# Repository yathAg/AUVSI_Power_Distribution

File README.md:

# AUVSI_Power_Distribution

This project includes the PCBS designed for the Seraphim , the Hex-rotor by PROJECT MANAS that participated in AUVSI SUAS 2022

The unavailibility of cheap and reliable power distribution systems called for designing a fully custom solution that powers the following :-
- Six T-Motor P60 170 Kv motors
- PixHawk Cube Orange
- RFD900X Telemetry Radio
- UGV Winch mechanism

The onboard electronic components are powered by
- Two 6S 32000 mAh LiPO Batteries for the Motors
- One 3S 4200 mAh LiPO Battery for control electronics

**The project includes three pcbs:**

## Power distribution pcb

A simple distributor pcb which can have upto 12 motors:
2 Oz thickness for more current
Exposed copper for heat sink
Voltage sense capability using the voltage from balance connector
Mosfets to shut down current flow when required

## Current sensing pcb  
This pcb is based on the allegro asc772 current sensor
The 400 amp variant was avoided due to unavailability
The 200 amp variant was chosen
2 boards will be used in order to measure separate packs in parallel
Output is a analog value of 5v
The board can also measure voltage levels

## Power HUB

This pcb incorporates the buck and boost modules
1x5v buck ( df13)
2x 5v buck ( ph)
1x 7.4v buck
Current sense mixer

The lmr33640 ic was chosen due to wide input range and 4 amp current output
All bucks were separated
Low space design
Can mix to current sensor values using opamp circuit
Reverse polarity protection

## Pcb design learnings from the project
- No thermals in high current pads
- Avoid choke points ( traces that make current flow path longer)
- Switching loops of power converters have to be as small as possible
- output trace thickness
- Placement of decoupling caps
- Using keepots to avoid traces being to close
- Appropriate pad sizes with vias for current conduction

All schematics , pcb images, and gerber files have been added
The gerbers were formatted for panelization

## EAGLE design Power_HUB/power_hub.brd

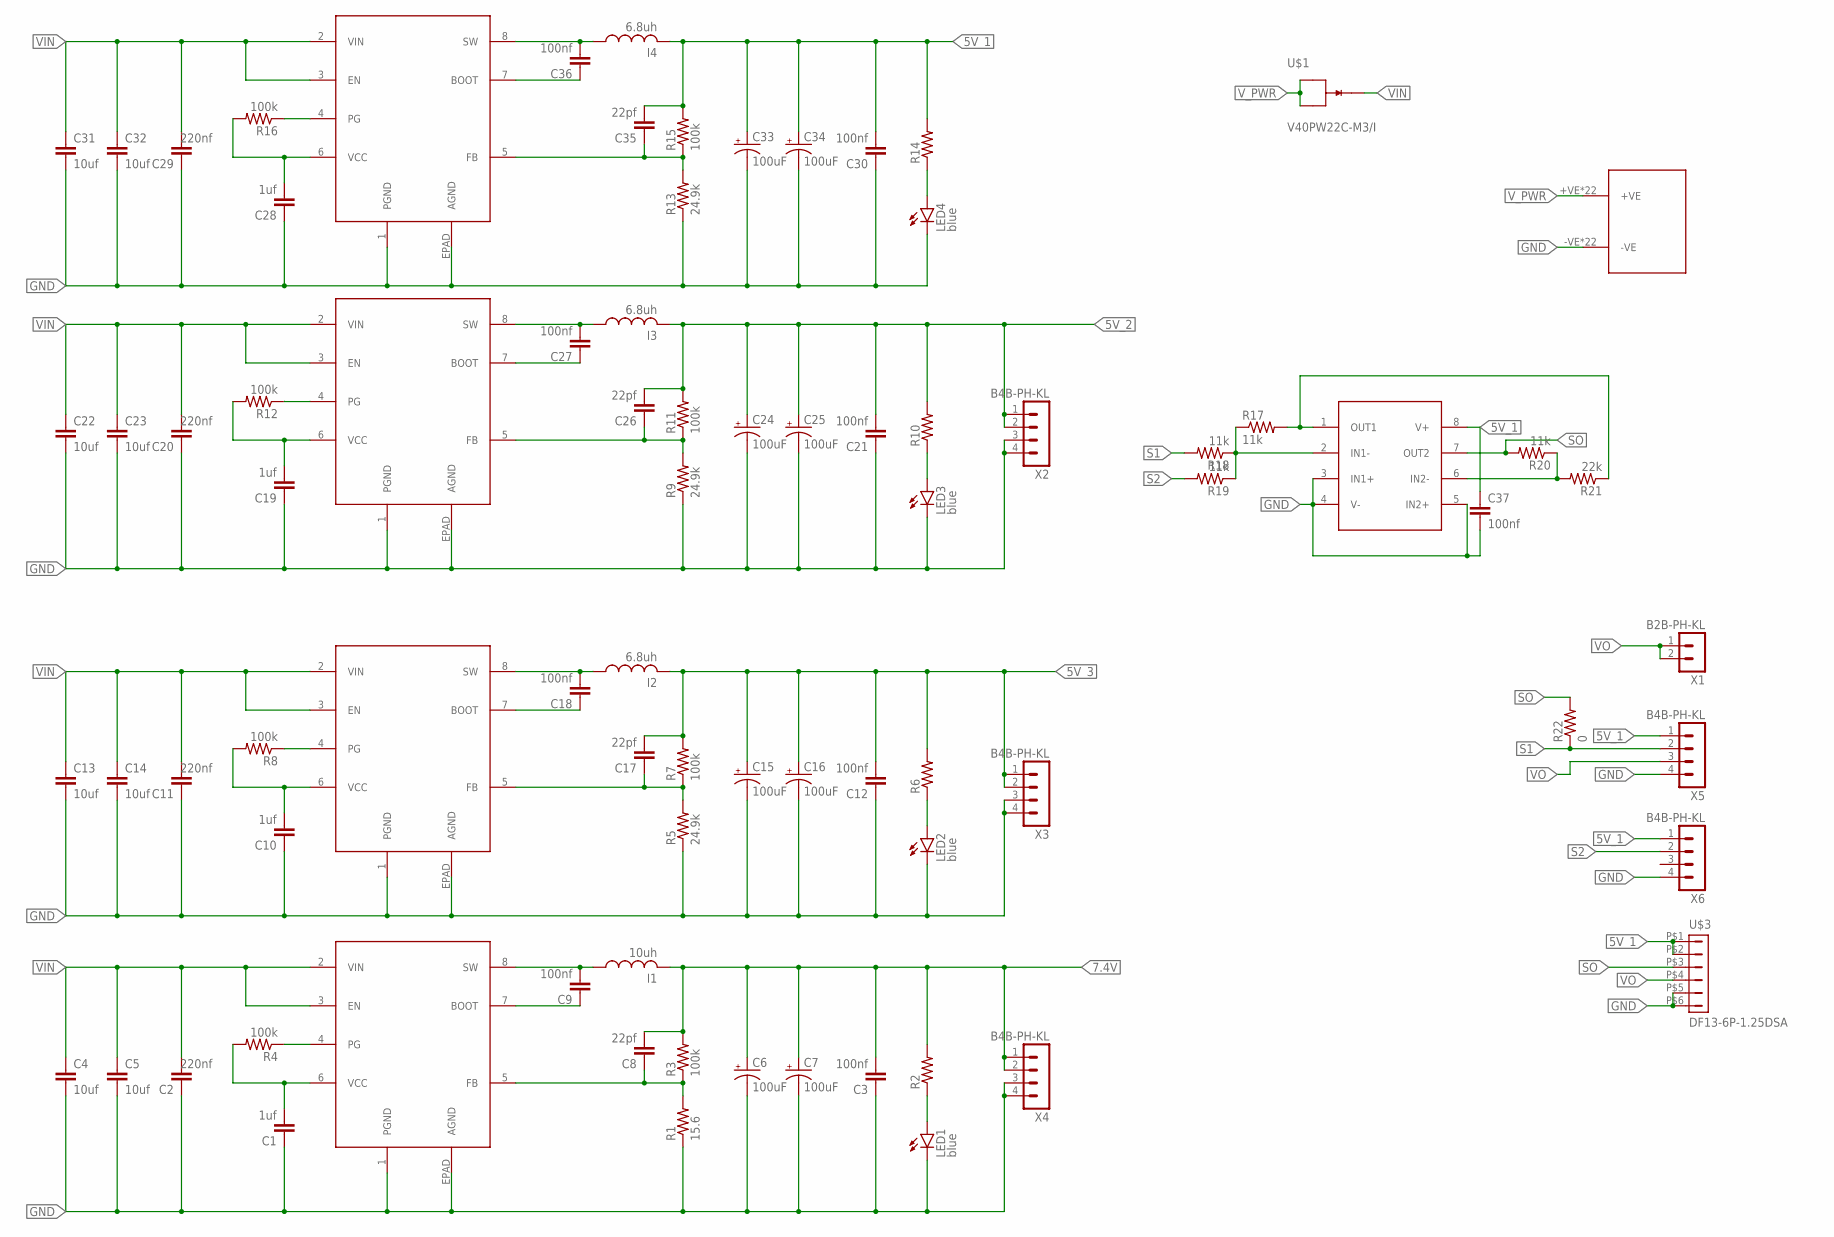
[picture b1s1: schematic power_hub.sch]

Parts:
C1, C10, C19, C28: 1uf; C0805
C2, C11, C20, C29: 220nf; C0805
C3, C9, C12, C18, C21, C27, C30, C36, C37: 100nf; C0805
C4, C5, C13, C14, C22, C23, C31, C32: 10uf; C1210
C6, C7, C15, C16, C24, C25, C33, C34: 100uF; PANASONIC_D
C8, C17, C26, C35: 22pf; C0805
I1: 10uh; INDUCTOR-1265
I2, I3, I4: 6.8uh; INDUCTOR-1265
LED1, LED2, LED3, LED4: blue; CHIPLED_0805
R1: 15.6; R0805
R2, R6, R10, R14: 1k; R0805
R3, R4, R7, R8, R11, R12, R15, R16: 100k; R0805
R5, R9, R13: 24.9k; R0805
R17, R18, R19, R20: 11k; R0805
R21: 22k; R0805
R22: 0; R0805
U1, U2, U3, U4: LMR33640; SO-POWERPAD8_DDA_TEX-M
U$1: V40PW22C-M3/I; TO-252AE
U$2: LM3588; SOP-08
U$3: DF13-6P-1.25DSA
U$4: CON_PAD; MOTOR_PAD
X1: B2B-PH-KL; B2B-PH-K-S
X2, X3, X4, X5, X6: B4B-PH-KL; B4B-PH-K-S

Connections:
5V_1: C30.2, C33.+, C34.+, C35.2, C37.1, I4.P$2 (2), R14.2, R15.2, U$2.8 (V+), U$3.P$1 (1), U$3.P$2 (2), X5.1, X6.1
5V_2: C21.2, C24.+, C25.+, C26.2, I3.P$2 (2), R10.2, R11.2, X2.1, X2.2
5V_3: C12.2, C15.+, C16.+, C17.2, I2.P$2 (2), R6.2, R7.2, X3.1, X3.2
7.4V: C3.2, C6.+, C7.+, C8.2, I1.P$2 (2), R2.2, R3.2, X4.1, X4.2
GND: C1.1, C2.1, C3.1, C4.2, C5.2, C6.-, C7.-, C10.1, C11.1, C12.1, C13.2, C14.2, C15.-, C16.-, C19.1, C20.1, C21.1, C22.2, C23.2, C24.-, C25.-, C28.1, C29.1, C30.1, C31.2, C32.2, C33.-, C34.-, C37.2, LED1.C, LED2.C, LED3.C, LED4.C, R1.1, R5.1, R9.1, R13.1, U1.1 (PGND), U1.EPAD (AGND), U2.1 (PGND), U2.EPAD (AGND), U3.1 (PGND), U3.EPAD (AGND), U4.1 (PGND), U4.EPAD (AGND), U$2.3 (IN1+), U$2.4 (V-), U$2.5 (IN2+), U$3.P$5 (5), U$3.P$6 (6), U$4.-VE, U$4.-VE_1 (-VE), U$4.V37 (-VE), U$4.V38 (-VE), U$4.V39 (-VE), U$4.V40 (-VE), U$4.V41 (-VE), U$4.V42 (-VE), U$4.V43 (-VE), U$4.V44 (-VE), U$4.V45 (-VE), U$4.V46 (-VE), U$4.V47 (-VE), U$4.V48 (-VE), U$4.V49 (-VE), U$4.V50 (-VE), U$4.V51 (-VE), U$4.V52 (-VE), U$4.V53 (-VE), U$4.V54 (-VE), U$4.V55 (-VE), U$4.V56 (-VE), X2.3, X2.4, X3.3, X3.4, X4.3, X4.4, X5.4, X6.4
unnamed: R17.1, R18.1, R19.1, U$2.2 (IN1-)
unnamed: R20.1, R21.2, U$2.6 (IN2-)
unnamed: R17.2, R21.1, U$2.1 (OUT1)
unnamed: C36.1, U4.7 (BOOT)
unnamed: C36.2, I4.P$1 (1), U4.8 (SW)
unnamed: C35.1, R13.2, R15.1, U4.5 (FB)
unnamed: C28.2, R16.2, U4.6 (VCC)
unnamed: R16.1, U4.4 (PG)
unnamed: LED4.A, R14.1
unnamed: C18.1, U2.7 (BOOT)
unnamed: C18.2, I2.P$1 (1), U2.8 (SW)
unnamed: C17.1, R5.2, R7.1, U2.5 (FB)
unnamed: C10.2, R8.2, U2.6 (VCC)
unnamed: R8.1, U2.4 (PG)
unnamed: LED2.A, R6.1
unnamed: C27.1, U3.7 (BOOT)
unnamed: C27.2, I3.P$1 (1), U3.8 (SW)
unnamed: C26.1, R9.2, R11.1, U3.5 (FB)
unnamed: C19.2, R12.2, U3.6 (VCC)
unnamed: R12.1, U3.4 (PG)
unnamed: LED3.A, R10.1
unnamed: C9.1, U1.7 (BOOT)
unnamed: C9.2, I1.P$1 (1), U1.8 (SW)
unnamed: C8.1, R1.2, R3.1, U1.5 (FB)
unnamed: C1.2, R4.2, U1.6 (VCC)
unnamed: R4.1, U1.4 (PG)
unnamed: LED1.A, R2.1
S1: R18.2, R22.1, X5.2
S2: R19.2, X6.2
SO: R20.2, R22.2, U$2.7 (OUT2), U$3.P$3 (3)
VIN: C2.2, C4.1, C5.1, C11.2, C13.1, C14.1, C20.2, C22.1, C23.1, C29.2, C31.1, C32.1, U1.2 (VIN), U1.3 (EN), U2.2 (VIN), U2.3 (EN), U3.2 (VIN), U3.3 (EN), U4.2 (VIN), U4.3 (EN), U$1.P$1 (K)
VO: U$3.P$4 (4), X1.1, X1.2, X5.3
V_PWR: U$1.P$2 (A1), U$1.P$3 (A2), U$4.+VE, U$4.+VE_1 (+VE), U$4.V7 (+VE), U$4.V8 (+VE), U$4.V9 (+VE), U$4.V10 (+VE), U$4.V11 (+VE), U$4.V12 (+VE), U$4.V13 (+VE), U$4.V14 (+VE), U$4.V15 (+VE), U$4.V16 (+VE), U$4.V17 (+VE), U$4.V18 (+VE), U$4.V19 (+VE), U$4.V20 (+VE), U$4.V21 (+VE), U$4.V22 (+VE), U$4.V23 (+VE), U$4.V24 (+VE), U$4.V25 (+VE), U$4.V26 (+VE)

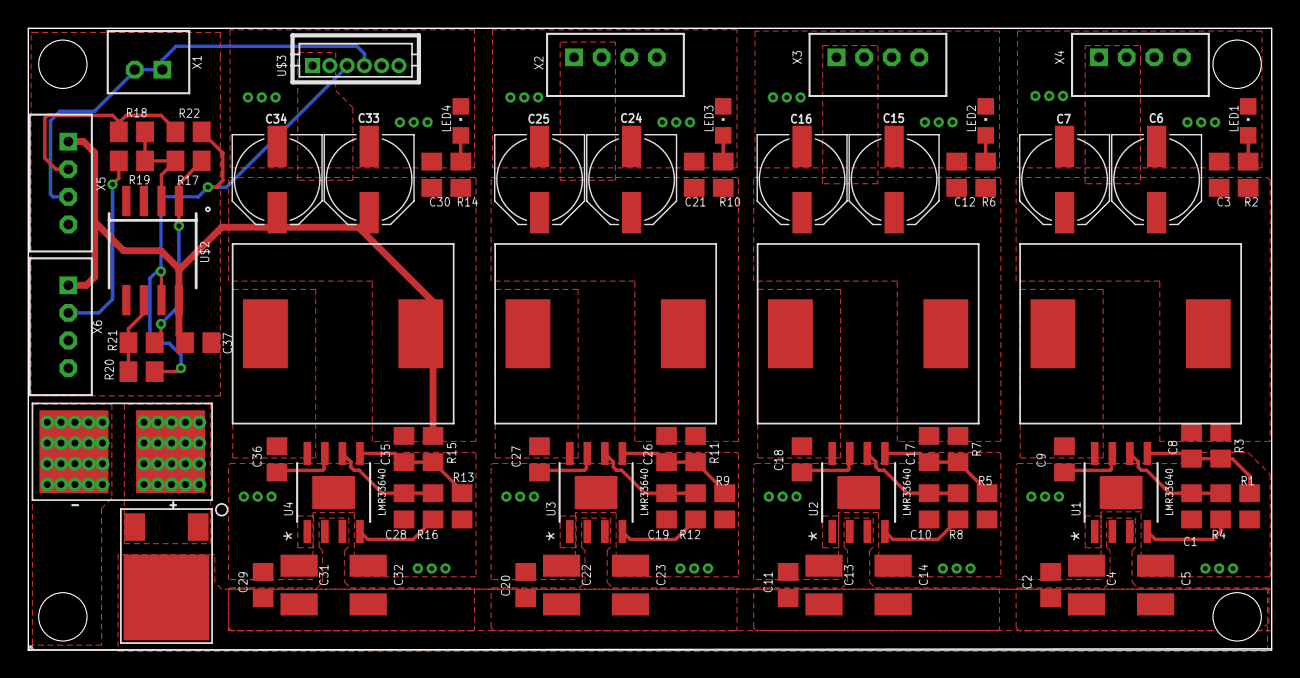
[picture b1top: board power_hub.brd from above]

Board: 2 copper layers, 90.0 x 45.0 mm, 81 parts (0 on the bottom side), 38 nets.

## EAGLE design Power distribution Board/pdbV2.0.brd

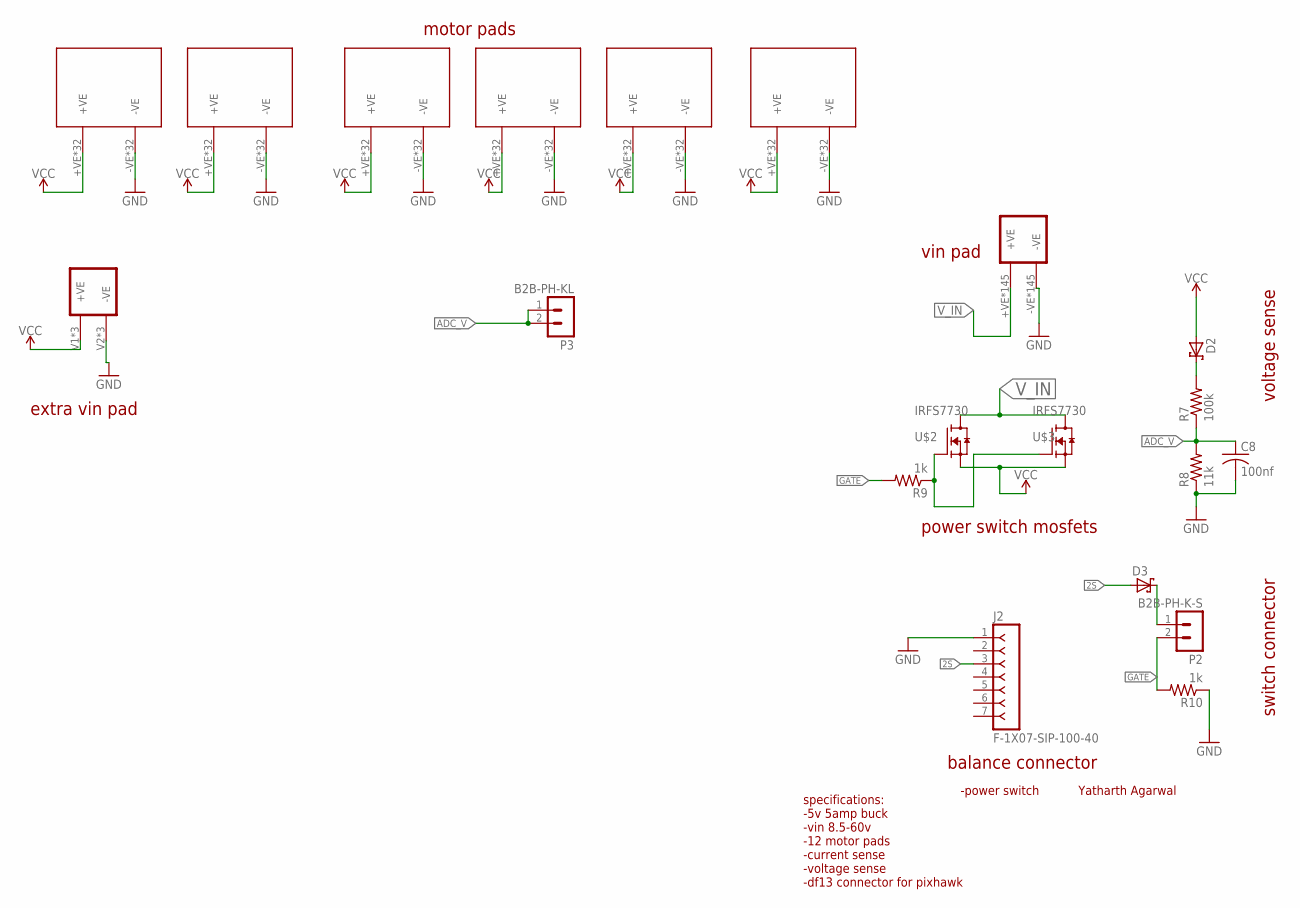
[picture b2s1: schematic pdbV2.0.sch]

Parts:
C8: 100nf; C0805
D2, D3: 1PS76SB70,115; SOD323(F)
J2: F-1X07-SIP-100-40; SIP-100-07-40
P2: B2B-PH-K-S
P3: B2B-PH-KL; B2B-PH-K-S
R7: 100k; R0805
R8: 11k; R0805
R9, R10: 1k; R0805
T1: BATTERY_PAD
T2, T3, T4, T5, T6, T7: MOTOR_PAD
U$1: CONPAD
U$2, U$3: IRFS7730; TO254P1524X457-3N

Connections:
2S: D3.2 (A), J2.3
ADC_V: C8.1, P3.1, P3.2, R7.1, R8.2
GATE: P2.2, R9.2, R10.2
GND: C8.2, J2.1, R8.1, R10.1, T1.-VE, T1.-VE_1 (-VE), T1.V109 (-VE), T1.V110 (-VE), T1.V111 (-VE), T1.V112 (-VE), T1.V113 (-VE), T1.V114 (-VE), T1.V115 (-VE), T1.V116 (-VE), T1.V117 (-VE), T1.V118 (-VE), T1.V119 (-VE), T1.V121 (-VE), T1.V122 (-VE), T1.V123 (-VE), T1.V124 (-VE), T1.V125 (-VE), T1.V126 (-VE), T1.V127 (-VE), T1.V128 (-VE), T1.V129 (-VE), T1.V130 (-VE), T1.V131 (-VE), T1.V133 (-VE), T1.V134 (-VE), T1.V135 (-VE), T1.V136 (-VE), T1.V137 (-VE), T1.V138 (-VE), T1.V139 (-VE), T1.V140 (-VE), T1.V141 (-VE), T1.V142 (-VE), T1.V143 (-VE), T1.V145 (-VE), T1.V146 (-VE), T1.V147 (-VE), T1.V148 (-VE), T1.V149 (-VE), T1.V150 (-VE), T1.V151 (-VE), T1.V152 (-VE), T1.V153 (-VE), T1.V154 (-VE), T1.V155 (-VE), T1.V157 (-VE), T1.V158 (-VE), T1.V159 (-VE), T1.V160 (-VE), T1.V161 (-VE), T1.V162 (-VE), T1.V163 (-VE), T1.V164 (-VE), T1.V165 (-VE), T1.V166 (-VE), T1.V167 (-VE), T1.V169 (-VE), T1.V170 (-VE), T1.V171 (-VE), T1.V172 (-VE), T1.V173 (-VE), T1.V174 (-VE), T1.V175 (-VE), T1.V176 (-VE), T1.V177 (-VE), T1.V178 (-VE), T1.V179 (-VE), T1.V181 (-VE), T1.V182 (-VE), T1.V183 (-VE), T1.V184 (-VE), T1.V185 (-VE), T1.V186 (-VE), T1.V187 (-VE), T1.V188 (-VE), T1.V189 (-VE), T1.V190 (-VE), T1.V191 (-VE), T1.V193 (-VE), T1.V194 (-VE), T1.V195 (-VE), T1.V196 (-VE), T1.V197 (-VE), T1.V198 (-VE), T1.V199 (-VE), T1.V200 (-VE), T1.V201 (-VE), T1.V202 (-VE), T1.V203 (-VE), T1.V232 (-VE), T1.V233 (-VE), T1.V234 (-VE), T1.V235 (-VE), T1.V236 (-VE), T1.V237 (-VE), T1.V238 (-VE), T1.V239 (-VE), T1.V240 (-VE), T1.V241 (-VE), T1.V242 (-VE), T1.V243 (-VE), T1.V244 (-VE), T1.V245 (-VE), T1.V246 (-VE), T1.V247 (-VE), T1.V248 (-VE), T1.V249 (-VE), T1.V250 (-VE), T1.V251 (-VE), T1.V252 (-VE), T1.V253 (-VE), T1.V254 (-VE), T1.V255 (-VE), T1.V256 (-VE), T1.V257 (-VE), T1.V258 (-VE), T1.V259 (-VE), T1.V260 (-VE), T1.V261 (-VE), T1.V262 (-VE), T1.V263 (-VE), T1.V264 (-VE), T1.V265 (-VE), T1.V266 (-VE), T1.V267 (-VE), T1.V268 (-VE), T1.V269 (-VE), T1.V270 (-VE), T1.V271 (-VE), T1.V272 (-VE), T1.V273 (-VE), T1.V274 (-VE), T1.V275 (-VE), T1.V276 (-VE), T1.V277 (-VE), T1.V278 (-VE), T1.V279 (-VE), T1.V280 (-VE), T1.V281 (-VE), T1.V282 (-VE), T1.V283 (-VE), T1.V284 (-VE), T1.V285 (-VE), T1.V286 (-VE), T2.-VE, T2.-VE_1 (-VE), T2.V32 (-VE), T2.V33 (-VE), T2.V34 (-VE), T2.V35 (-VE), T2.V36 (-VE), T2.V37 (-VE), T2.V38 (-VE), T2.V39 (-VE), T2.V40 (-VE), T2.V41 (-VE), T2.V42 (-VE), T2.V43 (-VE), T2.V44 (-VE), T2.V45 (-VE), T2.V46 (-VE), T2.V47 (-VE), T2.V48 (-VE), T2.V49 (-VE), T2.V50 (-VE), T2.V51 (-VE), T2.V52 (-VE), T2.V53 (-VE), T2.V54 (-VE), T2.V55 (-VE), T2.V56 (-VE), T2.V57 (-VE), T2.V58 (-VE), T2.V59 (-VE), T2.V60 (-VE), T2.V61 (-VE), T3.-VE, T3.-VE_1 (-VE), T3.V32 (-VE), T3.V33 (-VE), T3.V34 (-VE), T3.V35 (-VE), T3.V36 (-VE), T3.V37 (-VE), T3.V38 (-VE), T3.V39 (-VE), T3.V40 (-VE), T3.V41 (-VE), T3.V42 (-VE), T3.V43 (-VE), T3.V44 (-VE), T3.V45 (-VE), T3.V46 (-VE), T3.V47 (-VE), T3.V48 (-VE), T3.V49 (-VE), T3.V50 (-VE), T3.V51 (-VE), T3.V52 (-VE), T3.V53 (-VE), T3.V54 (-VE), T3.V55 (-VE), T3.V56 (-VE), T3.V57 (-VE), T3.V58 (-VE), T3.V59 (-VE), T3.V60 (-VE), T3.V61 (-VE), T4.-VE, T4.-VE_1 (-VE), T4.V32 (-VE), T4.V33 (-VE), T4.V34 (-VE), T4.V35 (-VE), T4.V36 (-VE), T4.V37 (-VE), T4.V38 (-VE), T4.V39 (-VE), T4.V40 (-VE), T4.V41 (-VE), T4.V42 (-VE), T4.V43 (-VE), T4.V44 (-VE), T4.V45 (-VE), T4.V46 (-VE), T4.V47 (-VE), T4.V48 (-VE), T4.V49 (-VE), T4.V50 (-VE), T4.V51 (-VE), T4.V52 (-VE), T4.V53 (-VE), T4.V54 (-VE), T4.V55 (-VE), T4.V56 (-VE), T4.V57 (-VE), T4.V58 (-VE), T4.V59 (-VE), T4.V60 (-VE), T4.V61 (-VE), T5.-VE, T5.-VE_1 (-VE), T5.V32 (-VE), T5.V33 (-VE), T5.V34 (-VE), T5.V35 (-VE), T5.V36 (-VE), T5.V37 (-VE), T5.V38 (-VE), T5.V39 (-VE), T5.V40 (-VE), T5.V41 (-VE), T5.V42 (-VE), T5.V43 (-VE), T5.V44 (-VE), T5.V45 (-VE), T5.V46 (-VE), T5.V47 (-VE), T5.V48 (-VE), T5.V49 (-VE), T5.V50 (-VE), T5.V51 (-VE), T5.V52 (-VE), T5.V53 (-VE), T5.V54 (-VE), T5.V55 (-VE), T5.V56 (-VE), T5.V57 (-VE), T5.V58 (-VE), T5.V59 (-VE), T5.V60 (-VE), T5.V61 (-VE), T6.-VE, T6.-VE_1 (-VE), T6.V32 (-VE), T6.V33 (-VE), T6.V34 (-VE), T6.V35 (-VE), T6.V36 (-VE), T6.V37 (-VE), T6.V38 (-VE), T6.V39 (-VE), T6.V40 (-VE), T6.V41 (-VE), T6.V42 (-VE), T6.V43 (-VE), T6.V44 (-VE), T6.V45 (-VE), T6.V46 (-VE), T6.V47 (-VE), T6.V48 (-VE), T6.V49 (-VE), T6.V50 (-VE), T6.V51 (-VE), T6.V52 (-VE), T6.V53 (-VE), T6.V54 (-VE), T6.V55 (-VE), T6.V56 (-VE), T6.V57 (-VE), T6.V58 (-VE), T6.V59 (-VE), T6.V60 (-VE), T6.V61 (-VE), T7.-VE, T7.-VE_1 (-VE), T7.V32 (-VE), T7.V33 (-VE), T7.V34 (-VE), T7.V35 (-VE), T7.V36 (-VE), T7.V37 (-VE), T7.V38 (-VE), T7.V39 (-VE), T7.V40 (-VE), T7.V41 (-VE), T7.V42 (-VE), T7.V43 (-VE), T7.V44 (-VE), T7.V45 (-VE), T7.V46 (-VE), T7.V47 (-VE), T7.V48 (-VE), T7.V49 (-VE), T7.V50 (-VE), T7.V51 (-VE), T7.V52 (-VE), T7.V53 (-VE), T7.V54 (-VE), T7.V55 (-VE), T7.V56 (-VE), T7.V57 (-VE), T7.V58 (-VE), T7.V59 (-VE), T7.V60 (-VE), T7.V61 (-VE), U$1.V2 (-VE), U$1.V4 (-VE), U$1.V6 (-VE)
unnamed: D3.1 (K), P2.1
unnamed: D2.1 (K), R7.2
unnamed: R9.1, U$2.1 (G), U$3.1 (G)
VCC: D2.2 (A), T2.+VE, T2.+VE_1 (+VE), T2.V1 (+VE), T2.V3 (+VE), T2.V4 (+VE), T2.V5 (+VE), T2.V6 (+VE), T2.V7 (+VE), T2.V8 (+VE), T2.V9 (+VE), T2.V10 (+VE), T2.V11 (+VE), T2.V12 (+VE), T2.V13 (+VE), T2.V14 (+VE), T2.V15 (+VE), T2.V16 (+VE), T2.V17 (+VE), T2.V18 (+VE), T2.V19 (+VE), T2.V20 (+VE), T2.V21 (+VE), T2.V22 (+VE), T2.V23 (+VE), T2.V24 (+VE), T2.V25 (+VE), T2.V26 (+VE), T2.V27 (+VE), T2.V28 (+VE), T2.V29 (+VE), T2.V30 (+VE), T2.V31 (+VE), T3.+VE, T3.+VE_1 (+VE), T3.V1 (+VE), T3.V3 (+VE), T3.V4 (+VE), T3.V5 (+VE), T3.V6 (+VE), T3.V7 (+VE), T3.V8 (+VE), T3.V9 (+VE), T3.V10 (+VE), T3.V11 (+VE), T3.V12 (+VE), T3.V13 (+VE), T3.V14 (+VE), T3.V15 (+VE), T3.V16 (+VE), T3.V17 (+VE), T3.V18 (+VE), T3.V19 (+VE), T3.V20 (+VE), T3.V21 (+VE), T3.V22 (+VE), T3.V23 (+VE), T3.V24 (+VE), T3.V25 (+VE), T3.V26 (+VE), T3.V27 (+VE), T3.V28 (+VE), T3.V29 (+VE), T3.V30 (+VE), T3.V31 (+VE), T4.+VE, T4.+VE_1 (+VE), T4.V1 (+VE), T4.V3 (+VE), T4.V4 (+VE), T4.V5 (+VE), T4.V6 (+VE), T4.V7 (+VE), T4.V8 (+VE), T4.V9 (+VE), T4.V10 (+VE), T4.V11 (+VE), T4.V12 (+VE), T4.V13 (+VE), T4.V14 (+VE), T4.V15 (+VE), T4.V16 (+VE), T4.V17 (+VE), T4.V18 (+VE), T4.V19 (+VE), T4.V20 (+VE), T4.V21 (+VE), T4.V22 (+VE), T4.V23 (+VE), T4.V24 (+VE), T4.V25 (+VE), T4.V26 (+VE), T4.V27 (+VE), T4.V28 (+VE), T4.V29 (+VE), T4.V30 (+VE), T4.V31 (+VE), T5.+VE, T5.+VE_1 (+VE), T5.V1 (+VE), T5.V3 (+VE), T5.V4 (+VE), T5.V5 (+VE), T5.V6 (+VE), T5.V7 (+VE), T5.V8 (+VE), T5.V9 (+VE), T5.V10 (+VE), T5.V11 (+VE), T5.V12 (+VE), T5.V13 (+VE), T5.V14 (+VE), T5.V15 (+VE), T5.V16 (+VE), T5.V17 (+VE), T5.V18 (+VE), T5.V19 (+VE), T5.V20 (+VE), T5.V21 (+VE), T5.V22 (+VE), T5.V23 (+VE), T5.V24 (+VE), T5.V25 (+VE), T5.V26 (+VE), T5.V27 (+VE), T5.V28 (+VE), T5.V29 (+VE), T5.V30 (+VE), T5.V31 (+VE), T6.+VE, T6.+VE_1 (+VE), T6.V1 (+VE), T6.V3 (+VE), T6.V4 (+VE), T6.V5 (+VE), T6.V6 (+VE), T6.V7 (+VE), T6.V8 (+VE), T6.V9 (+VE), T6.V10 (+VE), T6.V11 (+VE), T6.V12 (+VE), T6.V13 (+VE), T6.V14 (+VE), T6.V15 (+VE), T6.V16 (+VE), T6.V17 (+VE), T6.V18 (+VE), T6.V19 (+VE), T6.V20 (+VE), T6.V21 (+VE), T6.V22 (+VE), T6.V23 (+VE), T6.V24 (+VE), T6.V25 (+VE), T6.V26 (+VE), T6.V27 (+VE), T6.V28 (+VE), T6.V29 (+VE), T6.V30 (+VE), T6.V31 (+VE), T7.+VE, T7.+VE_1 (+VE), T7.V1 (+VE), T7.V3 (+VE), T7.V4 (+VE), T7.V5 (+VE), T7.V6 (+VE), T7.V7 (+VE), T7.V8 (+VE), T7.V9 (+VE), T7.V10 (+VE), T7.V11 (+VE), T7.V12 (+VE), T7.V13 (+VE), T7.V14 (+VE), T7.V15 (+VE), T7.V16 (+VE), T7.V17 (+VE), T7.V18 (+VE), T7.V19 (+VE), T7.V20 (+VE), T7.V21 (+VE), T7.V22 (+VE), T7.V23 (+VE), T7.V24 (+VE), T7.V25 (+VE), T7.V26 (+VE), T7.V27 (+VE), T7.V28 (+VE), T7.V29 (+VE), T7.V30 (+VE), T7.V31 (+VE), U$1.V1 (+VE), U$1.V3 (+VE), U$1.V5 (+VE), U$2.3 (S), U$3.3 (S)
V_IN: T1.+VE, T1.+VE_1 (+VE), T1.V1 (+VE), T1.V2 (+VE), T1.V3 (+VE), T1.V4 (+VE), T1.V5 (+VE), T1.V6 (+VE), T1.V7 (+VE), T1.V8 (+VE), T1.V9 (+VE), T1.V10 (+VE), T1.V11 (+VE), T1.V12 (+VE), T1.V13 (+VE), T1.V14 (+VE), T1.V15 (+VE), T1.V16 (+VE), T1.V17 (+VE), T1.V18 (+VE), T1.V19 (+VE), T1.V20 (+VE), T1.V21 (+VE), T1.V22 (+VE), T1.V23 (+VE), T1.V24 (+VE), T1.V25 (+VE), T1.V26 (+VE), T1.V27 (+VE), T1.V28 (+VE), T1.V29 (+VE), T1.V30 (+VE), T1.V31 (+VE), T1.V32 (+VE), T1.V33 (+VE), T1.V34 (+VE), T1.V35 (+VE), T1.V36 (+VE), T1.V37 (+VE), T1.V38 (+VE), T1.V39 (+VE), T1.V40 (+VE), T1.V41 (+VE), T1.V42 (+VE), T1.V43 (+VE), T1.V44 (+VE), T1.V45 (+VE), T1.V46 (+VE), T1.V47 (+VE), T1.V48 (+VE), T1.V49 (+VE), T1.V50 (+VE), T1.V51 (+VE), T1.V52 (+VE), T1.V53 (+VE), T1.V54 (+VE), T1.V55 (+VE), T1.V56 (+VE), T1.V57 (+VE), T1.V58 (+VE), T1.V59 (+VE), T1.V60 (+VE), T1.V61 (+VE), T1.V62 (+VE), T1.V63 (+VE), T1.V64 (+VE), T1.V65 (+VE), T1.V66 (+VE), T1.V67 (+VE), T1.V68 (+VE), T1.V69 (+VE), T1.V70 (+VE), T1.V71 (+VE), T1.V72 (+VE), T1.V73 (+VE), T1.V74 (+VE), T1.V75 (+VE), T1.V76 (+VE), T1.V77 (+VE), T1.V78 (+VE), T1.V79 (+VE), T1.V80 (+VE), T1.V81 (+VE), T1.V82 (+VE), T1.V83 (+VE), T1.V84 (+VE), T1.V85 (+VE), T1.V86 (+VE), T1.V87 (+VE), T1.V88 (+VE), T1.V89 (+VE), T1.V90 (+VE), T1.V91 (+VE), T1.V92 (+VE), T1.V93 (+VE), T1.V94 (+VE), T1.V95 (+VE), T1.V96 (+VE), T1.V97 (+VE), T1.V98 (+VE), T1.V99 (+VE), T1.V100 (+VE), T1.V101 (+VE), T1.V102 (+VE), T1.V103 (+VE), T1.V104 (+VE), T1.V105 (+VE), T1.V106 (+VE), T1.V107 (+VE), T1.V108 (+VE), T1.V120 (+VE), T1.V132 (+VE), T1.V144 (+VE), T1.V156 (+VE), T1.V168 (+VE), T1.V180 (+VE), T1.V192 (+VE), T1.V204 (+VE), T1.V205 (+VE), T1.V206 (+VE), T1.V207 (+VE), T1.V208 (+VE), T1.V209 (+VE), T1.V210 (+VE), T1.V211 (+VE), T1.V212 (+VE), T1.V213 (+VE), T1.V214 (+VE), T1.V215 (+VE), T1.V216 (+VE), T1.V217 (+VE), T1.V218 (+VE), T1.V219 (+VE), T1.V220 (+VE), T1.V221 (+VE), T1.V222 (+VE), T1.V223 (+VE), T1.V224 (+VE), T1.V225 (+VE), T1.V226 (+VE), T1.V227 (+VE), T1.V228 (+VE), T1.V229 (+VE), T1.V230 (+VE), T1.V231 (+VE), U$2.2 (D), U$3.2 (D)

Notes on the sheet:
specifications: -5v 5amp buck -vin 8.5-60v -12 motor pads -current sense -voltage sense -df13 connector for pixhawk
Yatharth Agarwal
motor pads
extra vin pad
vin pad
balance connector
voltage sense
power switch mosfets
switch connector
-power switch

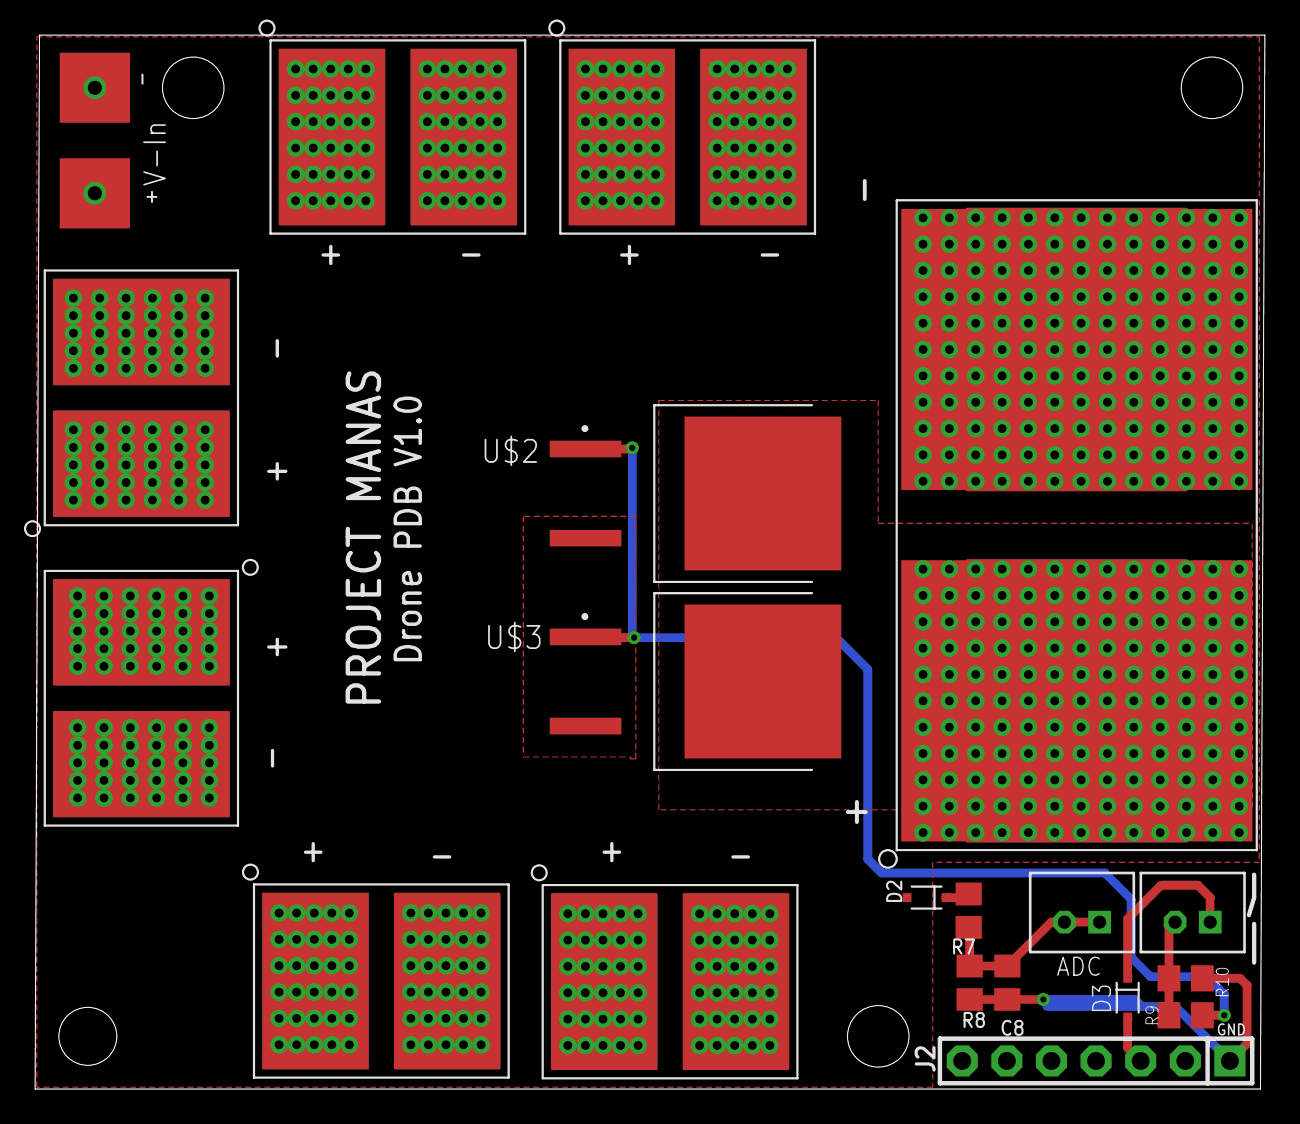
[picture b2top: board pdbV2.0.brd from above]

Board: 2 copper layers, 70.0 x 60.0 mm, 20 parts (0 on the bottom side), 9 nets.

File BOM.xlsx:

Qty | Value | Device | Package | Parts | Description
1 | 100k | R-US_R0805 | R0805 | R7 | RESISTOR, American symbol
1 | 100nf | C-USC0805 | C0805 | C8 | CAPACITOR, American symbol
1 | 11k | R-US_R0805 | R0805 | R8 | RESISTOR, American symbol
2 | 1PS76SB70,115 | 1PS76SB70,115 | SOD323(F) | D2, D3 | General-purpose Schottky diode General-purpose Schottky diodes in small Surface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
2 | 1k | R-US_R0805 | R0805 | R9, R10 | RESISTOR, American symbol
1 | B2B-PH-K-S | B2B-PH-K-S | B2B-PH-K-S | P2 | JST PH series header 2.00mm pitch disconnectable crimp style connectors, vertic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
1 | B2B-PH-KL | B2B-PH-KL | B2B-PH-K-S | P3 | JST PH series header 2.00mm pitch disconnectable crimp style connectors, vertic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
1 | F-1X07-SIP-100-40 | F-1X07-SIP-100-40 | SIP-100-07-40 | J2 | FEMALE HEADER
2 | IRFS7730 | IRFS7730 | TO254P1524X457-3N | U$2, U$3

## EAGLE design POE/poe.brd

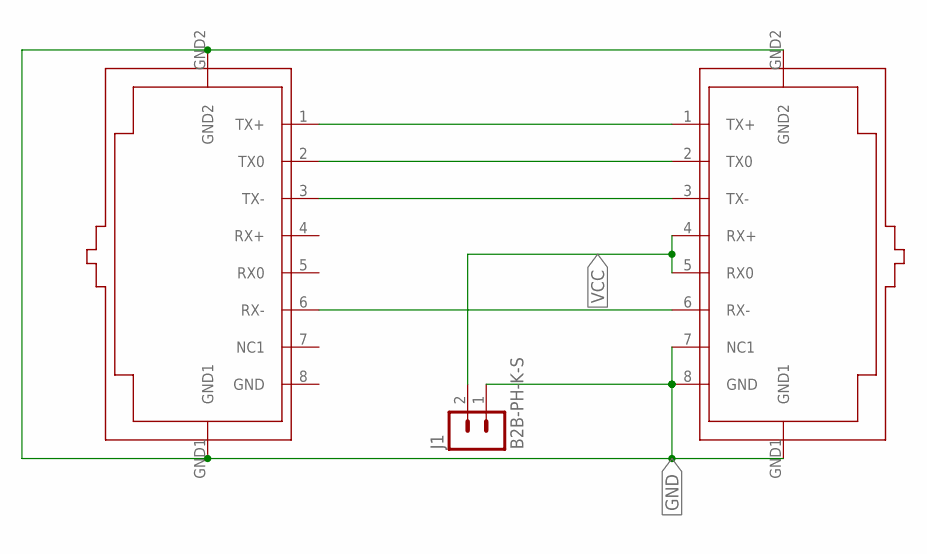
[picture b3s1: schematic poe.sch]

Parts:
J1: B2B-PH-K-S
U$1, U$2: RJ45-TRAFO

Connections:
GND: J1.1, U$1.GND1, U$1.GND2, U$2.7 (NC1), U$2.8 (GND), U$2.GND1, U$2.GND2
unnamed: U$1.1 (TX+), U$2.1 (TX+)
unnamed: U$1.2 (TX0), U$2.2 (TX0)
unnamed: U$1.3 (TX-), U$2.3 (TX-)
unnamed: U$1.6 (RX-), U$2.6 (RX-)
VCC: J1.2, U$2.4 (RX+), U$2.5 (RX0)

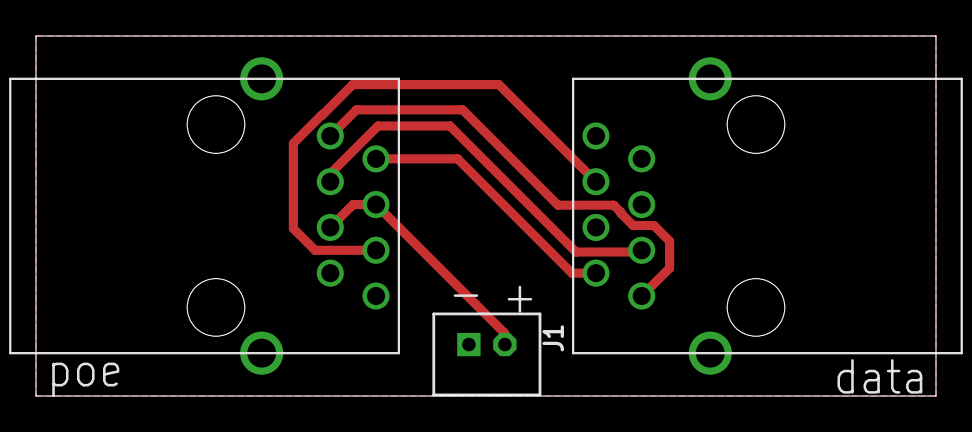
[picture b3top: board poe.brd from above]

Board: 2 copper layers, 50.0 x 20.0 mm, 3 parts (0 on the bottom side), 6 nets.

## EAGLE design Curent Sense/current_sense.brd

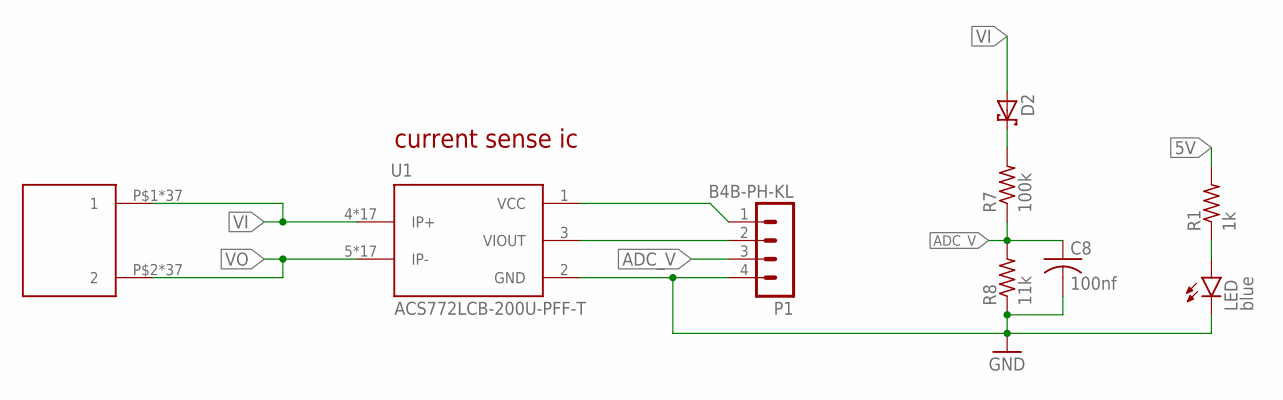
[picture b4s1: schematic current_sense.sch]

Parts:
C8: 100nf; C0805
D2: 1PS76SB70,115; SOD323(F)
LED: blue; CHIPLED_0805
P1: B4B-PH-KL; B4B-PH-K-S
R1: 1k; R0805
R7: 100k; R0805
R8: 11k; R0805
U1: ACS772LCB-200U-PFF-T; XDCR_ACS772LCB-100U-PFF-T
U$1: CON_PAD

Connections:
5V: P1.1, R1.2, U1.1 (VCC)
ADC_V: C8.1, P1.3, R7.1, R8.2
GND: C8.2, LED.C, P1.4, R8.1, U1.2 (GND)
unnamed: P1.2, U1.3 (VIOUT)
unnamed: LED.A, R1.1
unnamed: D2.1 (K), R7.2
VI: D2.2 (A), U1.4 (IP+), U1.4_1 (IP+), U1.4_2 (IP+), U1.4_3 (IP+), U1.4_4 (IP+), U1.4_5 (IP+), U1.4_6 (IP+), U1.4_7 (IP+), U1.4_8 (IP+), U1.4_9 (IP+), U1.4_10 (IP+), U1.4_11 (IP+), U1.4_12 (IP+), U1.4_13 (IP+), U1.4_14 (IP+), U1.4_15 (IP+), U1.4_16 (IP+), U$1.P$1 (1), U$1.P$3 (1), U$1.P$5 (1), U$1.P$6 (1), U$1.P$7 (1), U$1.P$8 (1), U$1.P$9 (1), U$1.P$10 (1), U$1.P$11 (1), U$1.P$12 (1), U$1.P$13 (1), U$1.P$14 (1), U$1.P$15 (1), U$1.P$16 (1), U$1.P$17 (1), U$1.P$18 (1), U$1.P$19 (1), U$1.P$20 (1), U$1.P$21 (1), U$1.P$22 (1), U$1.P$23 (1), U$1.P$24 (1), U$1.P$25 (1), U$1.P$26 (1), U$1.P$27 (1), U$1.P$28 (1), U$1.P$29 (1), U$1.P$30 (1), U$1.P$31 (1), U$1.P$32 (1), U$1.P$33 (1), U$1.P$34 (1), U$1.P$35 (1), U$1.P$36 (1), U$1.P$37 (1), U$1.P$38 (1), U$1.P$39 (1)
VO: U1.5 (IP-), U1.5_1 (IP-), U1.5_2 (IP-), U1.5_3 (IP-), U1.5_4 (IP-), U1.5_5 (IP-), U1.5_6 (IP-), U1.5_7 (IP-), U1.5_8 (IP-), U1.5_9 (IP-), U1.5_10 (IP-), U1.5_11 (IP-), U1.5_12 (IP-), U1.5_13 (IP-), U1.5_14 (IP-), U1.5_15 (IP-), U1.5_16 (IP-), U$1.P$2 (2), U$1.P$4 (2), U$1.P$40 (2), U$1.P$41 (2), U$1.P$42 (2), U$1.P$43 (2), U$1.P$44 (2), U$1.P$45 (2), U$1.P$46 (2), U$1.P$47 (2), U$1.P$48 (2), U$1.P$49 (2), U$1.P$50 (2), U$1.P$51 (2), U$1.P$52 (2), U$1.P$53 (2), U$1.P$54 (2), U$1.P$55 (2), U$1.P$56 (2), U$1.P$57 (2), U$1.P$58 (2), U$1.P$59 (2), U$1.P$60 (2), U$1.P$61 (2), U$1.P$62 (2), U$1.P$63 (2), U$1.P$64 (2), U$1.P$65 (2), U$1.P$66 (2), U$1.P$67 (2), U$1.P$68 (2), U$1.P$69 (2), U$1.P$70 (2), U$1.P$71 (2), U$1.P$72 (2), U$1.P$73 (2), U$1.P$74 (2)

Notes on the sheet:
current sense ic

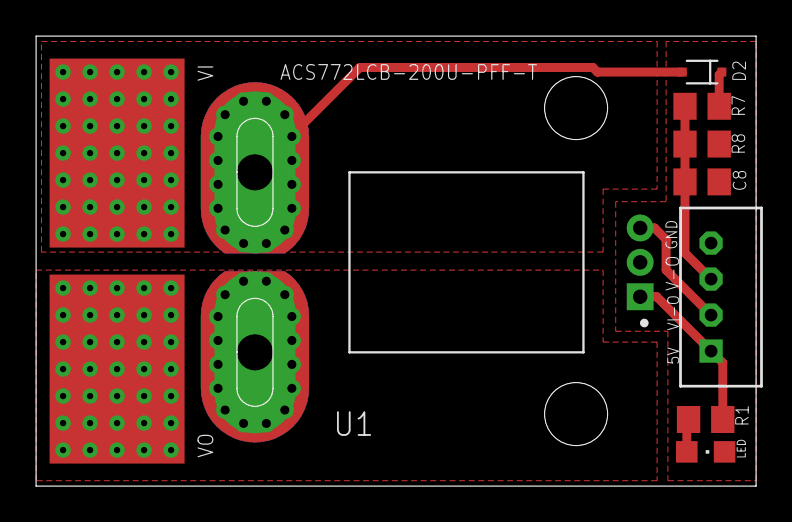
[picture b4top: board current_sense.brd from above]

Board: 2 copper layers, 40.0 x 25.0 mm, 9 parts (0 on the bottom side), 8 nets.

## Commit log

2022-09-10 folder names changed
2022-09-10 test
2022-09-10 Modified ReadMe

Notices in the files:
parts and their libraries:
con-headers-jp: Copyright (C) 2008, Bob Starr
SparkFun-PowerSymbols: Licensing: Creative Commons ShareAlike 4.0 International - https://creativecommons.org/licenses/by-sa/4.0
